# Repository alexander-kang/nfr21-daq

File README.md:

# NFR22's data acquisition system

Repository Contents
-------------------
* **Breakout** - EAGLE design files (.brd, .sch) for the pitot tube breakout board
* **Daughter** - EAGLE design files (.brd, .sch) for the intermediary daughter board
* **Images** - Images for the README's within this repository's subdirectories
* **Main** - EAGLE design files (.brd, .sch) for the main data acquisition board

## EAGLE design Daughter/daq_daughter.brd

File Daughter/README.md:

Board
-----
  
Schematic
---------

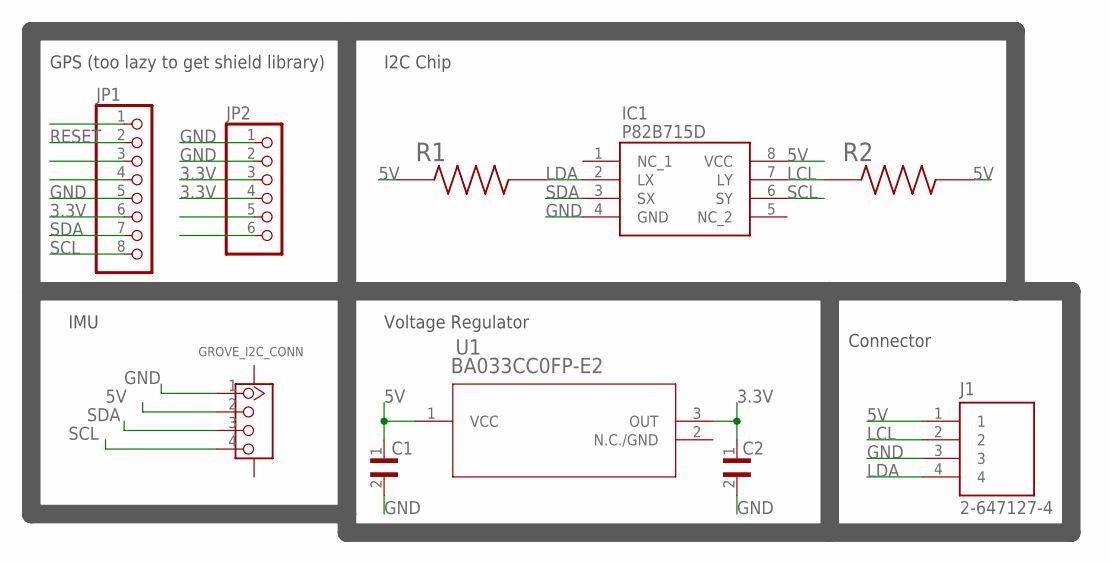
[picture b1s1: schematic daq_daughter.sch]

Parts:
C1, C2: C3216X5R1E106M085AC; CAPC3216X100N
GROVE_I2C_CONN: CONNECTOR-NEW_GROVE-CONNECTOR-SMDDD; CONNECTOR-NEW_HW4-SMD-2.0
IC1: P82B715D; SOIC127P600X175-8N
J1: 2-647127-4; TE_2-647127-4
JP1: PINHD-1X8M; 1X08M
JP2: PINHD-1X6M; 1X06M
R1, R2: RMCF1206JT10K0; RESC3216X70N
U1: BA033CC0FP-E2; TO252-3_ROM

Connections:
3.3V: C2.1, JP1.6, JP2.3, JP2.4, U1.3 (OUT)
5V: C1.1, GROVE_I2C_CONN.2, IC1.8 (VCC), J1.1, R1.1, R2.2, U1.1 (VCC)
GND: C1.2, C2.2, GROVE_I2C_CONN.1, IC1.4 (GND), J1.3, JP1.5, JP2.1, JP2.2
LCL: IC1.7 (LY), J1.2, R2.1
LDA: IC1.2 (LX), J1.4, R1.2
RESET: JP1.2
SCL: GROVE_I2C_CONN.4, IC1.6 (SY), JP1.8
SDA: GROVE_I2C_CONN.3, IC1.3 (SX), JP1.7

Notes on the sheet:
GPS (too lazy to get shield library)
IMU
I2C Chip
Connector
Voltage Regulator

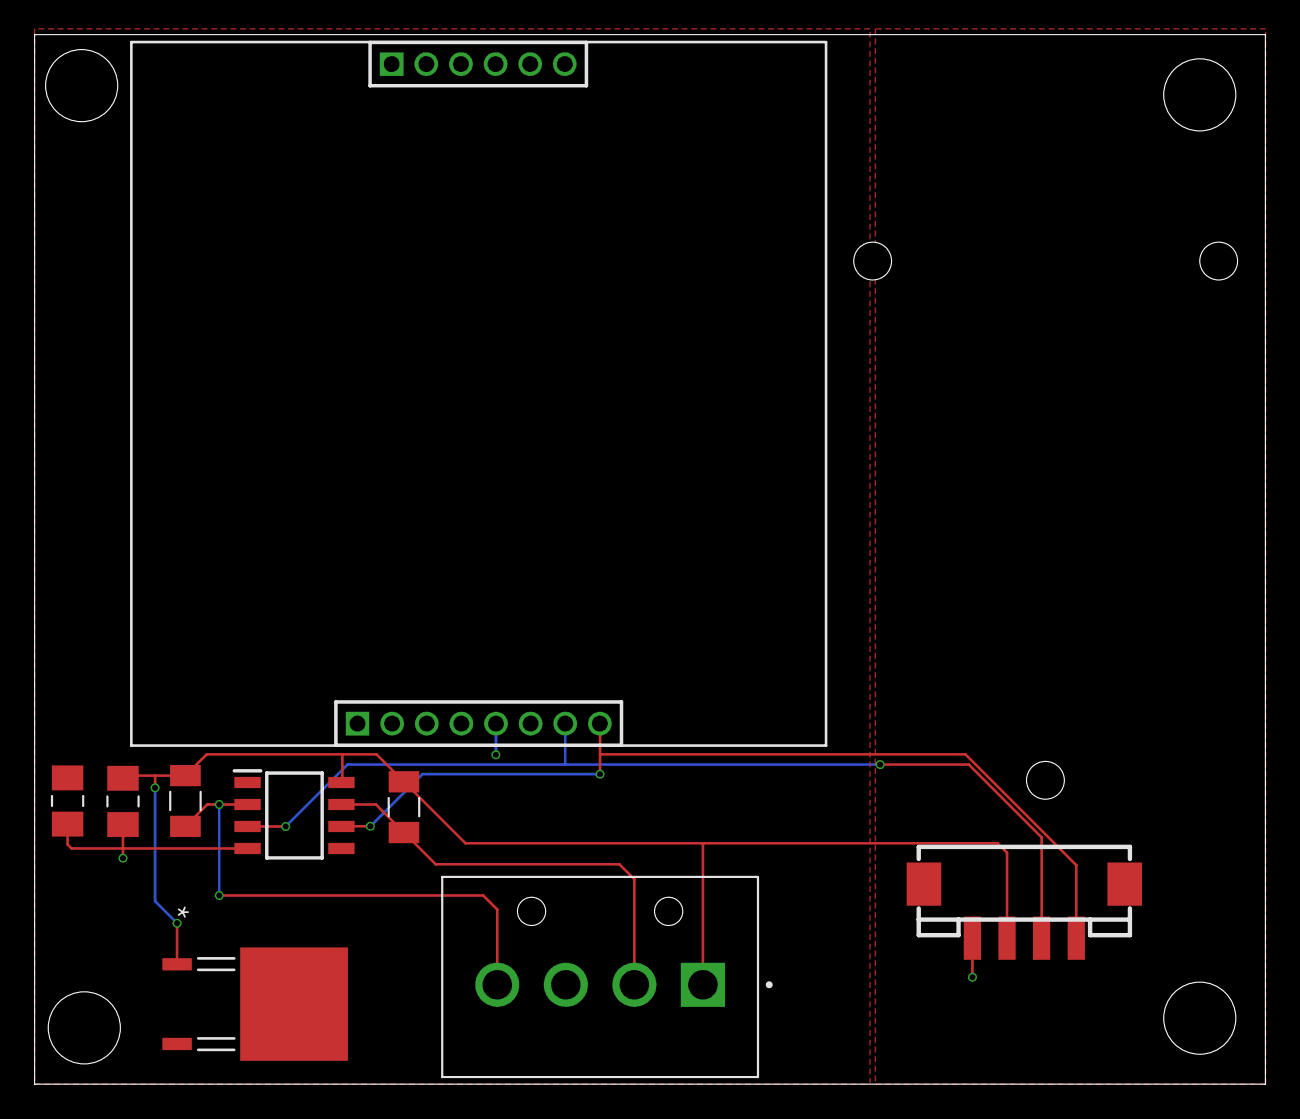
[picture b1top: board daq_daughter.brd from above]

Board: 2 copper layers, 71.1 x 60.6 mm, 10 parts (0 on the bottom side), 7 nets.

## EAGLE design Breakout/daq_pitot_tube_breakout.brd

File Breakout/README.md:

Board
-----
  
Schematic
---------

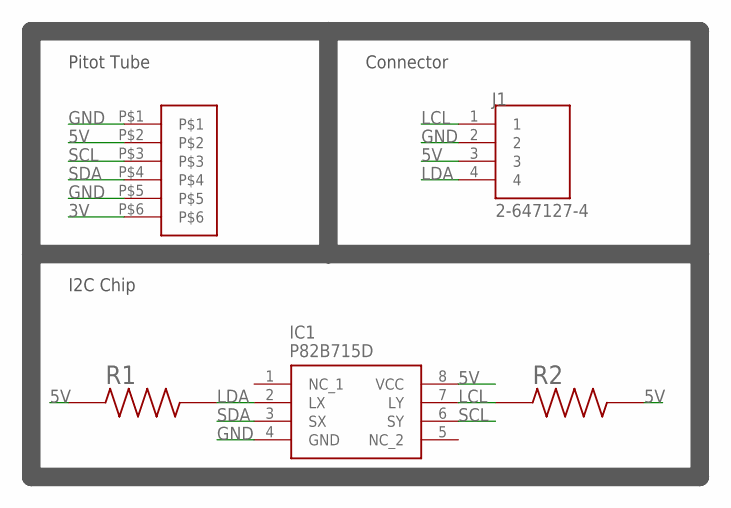
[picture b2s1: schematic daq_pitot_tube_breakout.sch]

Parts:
IC1: P82B715D; SOIC127P600X175-8N
J1: 2-647127-4; TE_2-647127-4
R1, R2: RMCF1206JT10K0; RESC3216X70N
U$1: ASPD-4525

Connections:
3V: U$1.P$6
5V: IC1.8 (VCC), J1.3, R1.1, R2.2, U$1.P$2
GND: IC1.4 (GND), J1.2, U$1.P$1, U$1.P$5
LCL: IC1.7 (LY), J1.1, R2.1
LDA: IC1.2 (LX), J1.4, R1.2
SCL: IC1.6 (SY), U$1.P$3
SDA: IC1.3 (SX), U$1.P$4

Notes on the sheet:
Pitot Tube
I2C Chip
Connector

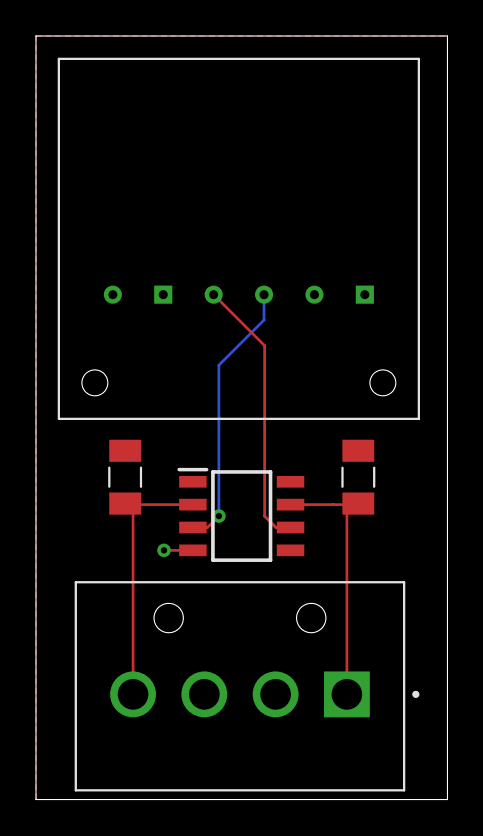
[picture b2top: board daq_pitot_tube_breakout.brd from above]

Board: 2 copper layers, 22.9 x 42.4 mm, 5 parts (0 on the bottom side), 6 nets.

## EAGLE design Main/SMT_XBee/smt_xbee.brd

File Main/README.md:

Directory Contents
------------------
* **SMT_XBee** - EAGLE design files (.brd, .sch) for the main board with a surface-mount XBee (telemetry radio module)
* **Throughhole_XBee** - EAGLE design files (.brd, .sch) for the main board with a through-hole XBee (telemetry radio module)

Board
-----
  
Schematic
---------

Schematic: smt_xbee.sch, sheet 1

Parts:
B1: ARDUINO_MEGA_R3FULL; ARDUINO_MEGA
BRAKEPRES: 156120M173000
BRAKETEMP: 156120M173000
C1, C2, C5, C26: 10μF; C1206
C3, C4: 8.2pF; C1206
C6, C7, C8, C9, C10, C11, C12, C13, C14, C15, C16, C17, C18, C19, C20, C21, C22, C23, C24, C25, C28, C29, C30, C31, C32, C33, C34, C35: 0.1μF; C1206
C27: 22μF; C1206
COOLANTTEMP: 156120M173000
DAQ: 156120M173000
DASH: 156120M173000
E*1: XBEE3PRO_SMT; XBEE3PRO_SMT_FOOTPRINT
IC1: P82B715D; SOIC127P600X175-8N
INTAKEPRES: 156120M173000
INTAKETEMP: 156120M173000
J1: 6473427-1; TE_6473427-1
J2: VR10S05; CONN3_10S05_XPP
JP1: DNP; 1X04
LAMBDAS: 156120M173000
OILPRES: 156120M173000
OILTEMP: 156120M173000
Q1, Q2: MOSFET-NCHANNELSMD; SOT23-3
R1, R2, R3, R4, R11, R12, R13, R14, R15, R16, R17, R18, R19, R20, R21, R22, R23, R24: 1kΩ; R1206
R5, R6, R7, R8, R9, R10, R25, R26, R27, R28, R29, R30, R31, R32, R33, R34, R35, R36, R37, R38, R39, R40, R41, R42, R43, R44, R45, R46, R47, R48, R49, R50, R51, R52, R53, R54, R55, R56, R57, R58, R71: 10kΩ; R1206
R59, R60, R61, R62, R63, R64, R65, R66, R67, R68, R69, R70: 350Ω; R1206
REC: SML-LX1206SIC-TR; LED_SML-LX1206SIC-TR_LUM
SHOCKPOT: 156120M173000
SPARE1, SPARE2: 156120M173000
SW1, SW2: CTS_ELECTROCOMPONENTS_204-211STCTS_ELECTROCOMPONE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; CTS_ELECTROCOMPONENTS_204-211ST_0
U1: XC6220B331MR-G; SOT-25_TOR
U6, U7: ADS1119IPWT; PW0016A_N

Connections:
2AIC0: C28.2, R51.1, U7.11 (AIN0)
2AIC1: C29.2, R52.1, U6.11 (AIN0)
2AIC2: C30.2, R53.1, U7.10 (AIN1)
2AIC3: C31.2, R54.1, U6.10 (AIN1)
3.3V: C2.1, C3.2, C4.2, C5.2, E*1.2, E*1.2-1 (2), R2.2, R4.2, R7.2, R8.1, U1.5 (VOUT)
3AIC0: C32.2, R55.1, U7.7 (AIN2)
3AIC1: C33.2, R56.1, U6.7 (AIN2)
3AIC2: C34.2, R57.1, U7.6 (AIN3)
3AIC3: C35.2, R58.1, U6.6 (AIN3)
4: B1.4, BRAKETEMP.4 (K_GREEN)
5: B1.5, DASH.2 (K_BLUE)
5V: B1.5V@0 (5V), C1.2, C22.2, C23.1, C24.2, C25.1, C27.2, IC1.8 (VCC), J1.12, J1.15, J2.3, JP1.1, Q1.1 (G), Q2.1 (G), R1.2, R3.2, R5.1, R9.1, R10.2, R11.2, R12.2, R13.2, R14.2, R15.2, R16.2, R17.2, R18.2, R19.2, R20.2, R21.2, R22.2, R23.2, R24.1, R41.1, R42.1, R43.2, R44.1, R45.1, R46.2, R47.1, R48.1, R49.1, R50.2, R60.1, R63.1, R66.1, R69.1, SW1.1, SW2.1, U1.1 (VIN), U6.3 (RESET_N), U6.12 (AVDD), U6.13 (DVDD), U7.3 (RESET_N), U7.12 (AVDD), U7.13 (DVDD); also elsewhere on the board
5VOR0V: R61.1, R64.1, R67.1, R70.1, SW1.2
6: B1.6, DASH.3 (K_RED)
7: B1.7, DASH.4 (K_GREEN)
8: B1.8, LAMBDAS.2 (K_BLUE)
9: B1.9, LAMBDAS.3 (K_RED)
10: B1.10, LAMBDAS.4 (K_GREEN)
12V: B1.VIN, C26.2, J1.26, J1.54, J2.1
14: B1.14 (14(TX3)), BRAKETEMP.3 (K_RED)
15: B1.15 (15(RX3)), BRAKETEMP.2 (K_BLUE)
16: B1.16 (16(TX2)), SHOCKPOT.4 (K_GREEN)
17: B1.17 (17(RX2)), SHOCKPOT.3 (K_RED)
18: B1.18 (18(TX1)), SHOCKPOT.2 (K_BLUE)
19: B1.19 (19(RX1)), BRAKEPRES.4 (K_GREEN)
22: B1.22, BRAKEPRES.3 (K_RED)
23: B1.23, BRAKEPRES.2 (K_BLUE)
24: B1.24, INTAKEPRES.4 (K_GREEN)
25: B1.25, INTAKEPRES.3 (K_RED)
26: B1.26, INTAKEPRES.2 (K_BLUE)
27: B1.27, INTAKETEMP.4 (K_GREEN)
28: B1.28, INTAKETEMP.3 (K_RED)
29: B1.29, INTAKETEMP.2 (K_BLUE)
30: B1.30, COOLANTTEMP.4 (K_GREEN)
31: B1.31, COOLANTTEMP.3 (K_RED)
32: B1.32, COOLANTTEMP.2 (K_BLUE)
33: B1.33, OILPRES.4 (K_GREEN)
34: B1.34, OILPRES.3 (K_RED)
35: B1.35, OILPRES.2 (K_BLUE)
36: B1.36, OILTEMP.4 (K_GREEN)
37: B1.37, OILTEMP.3 (K_RED)
38: B1.38, OILTEMP.2 (K_BLUE)
39: B1.39, SPARE1.4 (K_GREEN)
40: B1.40, SPARE1.3 (K_RED)
41: B1.41, SPARE1.2 (K_BLUE)
42: B1.42, SPARE2.4 (K_GREEN)
43: B1.43, SPARE2.3 (K_RED)
44: B1.44, SPARE2.2 (K_BLUE)
45: B1.45, DAQ.4 (K_GREEN)
46: B1.46, DAQ.3 (K_RED)
47: B1.47, DAQ.2 (K_BLUE)
48: B1.48, R71.1, SW2.2
A0: B1.A0 (A0(RX0)), C6.2, R25.2
A0IN: J1.18, R25.1
A1: B1.A1 (A1(TX0)), C7.2, R26.2
A1IN: J1.19, R26.1
A2: B1.A2, C8.2, R27.2
A2IN: J1.20, R27.1
A3: B1.A3, C9.2, R28.2
A3IN: J1.10, R28.1
A4: B1.A4, C10.2, R29.2
A4IN: J1.1, R29.1
A5: B1.A5, C11.2, R30.2
A5IN: J1.11, R30.1
A6: B1.A6, C12.2, R31.2
A6IN: J1.9, R31.1
A7: B1.A7, C13.2, R32.2
A7IN: J1.17, R32.1
A8: B1.A8, C14.2, R33.2
A8IN: J1.8, R33.1
A9: B1.A9, C15.2, R34.2
A9IN: J1.16, R34.1
A10: B1.A10, C16.2, R35.2
A10IN: J1.7, R35.1
A11: B1.A11, C17.2, R36.2
A11IN: J1.6, R36.1
A12: B1.A12, C18.2, R37.2
A12IN: J1.13, R37.1
A13: B1.A13, C19.2, R38.2
A13IN: J1.4, R38.1
A14: B1.A14, C20.2, R39.2
A14IN: J1.5, R39.1
A15: B1.A15, C21.2, R40.2
A15IN: J1.14, R40.1
CALIB: B1.13, J1.31, R50.1
CANHI: J1.60, JP1.3
CANLO: J1.53, JP1.4
CAN_CS: B1.49; also elsewhere on the board
DIN: E*1.4, E*1.4-1 (4), Q1.2 (S), R3.1
DOUT: E*1.3, E*1.3-1 (3), Q2.2 (S), R1.1
FL_WS: B1.2, J1.25, R47.2
FR_WS: B1.3, J1.34, R48.2
GND: B1.GND@0 (GND), C1.1, C2.2, C3.1, C4.1, C5.1, C6.1, C7.1, C8.1, C9.1, C10.1, C11.1, C12.1, C13.1, C14.1, C15.1, C16.1, C17.1, C18.1, C19.1, C20.1, C21.1, C22.1, C23.2, C24.1, C25.2, C26.1, C27.1, C28.1, C29.1, C30.1, C31.1, C32.1, C33.1, C34.1, C35.1, E*1.1, E*1.1-1 (1), E*1.11, E*1.11-1 (11), E*1.13, E*1.13-1 (13), E*1.22, E*1.22-1 (22), E*1.35, E*1.35-1 (35), E*1.38 (0), E*1.38-1 (0), E*1.38-2 (0), E*1.38-3 (0), E*1.38-4 (0), E*1.38-5 (0), E*1.38-6 (0), E*1.38-7 (0), E*1.38-8 (0), E*1.38-9 (0), IC1.4 (GND), J1.21, J1.22, J1.23, J1.24, J1.50, J1.51, J1.52, J2.2, JP1.2, R6.1, R59.2, R62.2, R65.2, R68.2, R71.2, U1.2 (VSS), U6.4 (DGND), U6.5 (AGND), U7.4 (DGND), U7.5 (AGND); also elsewhere on the board
LCL: IC1.7 (LY), J1.35, J1.36, J1.37, J1.38, J1.39, J1.40, J1.41, J1.42, J1.43, J1.44, J1.45, J1.46, J1.47, J1.48, J1.49, J1.57, R10.1
LDA: IC1.2 (LX), J1.32, R9.2
MISO: B1.50; also elsewhere on the board
MOSI: B1.51; also elsewhere on the board
unnamed: INTAKEPRES.1 (COMMON_ANODE), R16.1
unnamed: R5.2, R6.2, U1.3 (CE)
unnamed: DASH.1 (COMMON_ANODE), R11.1
unnamed: INTAKETEMP.1 (COMMON_ANODE), R17.1
unnamed: COOLANTTEMP.1 (COMMON_ANODE), R18.1
unnamed: OILPRES.1 (COMMON_ANODE), R19.1
unnamed: OILTEMP.1 (COMMON_ANODE), R20.1
unnamed: R21.1, SPARE1.1 (COMMON_ANODE)
unnamed: R22.1, SPARE2.1 (COMMON_ANODE)
unnamed: DAQ.1 (COMMON_ANODE), R23.1
unnamed: R24.2, REC.2
unnamed: E*1.10, E*1.10-1 (10), R8.2
unnamed: R43.1, U6.14 (DRDY_N)
unnamed: LAMBDAS.1 (COMMON_ANODE), R12.1
unnamed: BRAKETEMP.1 (COMMON_ANODE), R13.1
unnamed: R14.1, SHOCKPOT.1 (COMMON_ANODE)
unnamed: BRAKEPRES.1 (COMMON_ANODE), R15.1
unnamed: E*1.29, E*1.29-1 (29), R7.1
unnamed: R51.2, R59.1, R60.2
unnamed: R53.2, R62.1, R63.2
unnamed: R46.1, U7.14 (DRDY_N)
unnamed: R55.2, R65.1, R66.2
unnamed: R41.2, U6.9 (REFP)
unnamed: R42.2, U6.8 (REFN)
unnamed: R44.2, U7.9 (REFP)
unnamed: R45.2, U7.8 (REFN)
unnamed: R57.2, R68.1, R69.2
REC: B1.11, J1.33, R49.2, REC.1
RX0: B1.0 (0(RX0)), Q2.3 (D), R2.1
SCK: B1.52; also elsewhere on the board
SCL: B1.21 (21(SCL)), IC1.6 (SY), U6.2 (A1), U6.16 (SCL), U7.1 (A0), U7.16 (SCL)
SDA: B1.20 (20(SDA)), IC1.3 (SX), U6.1 (A0), U6.15 (SDA), U7.2 (A1), U7.15 (SDA)
SD_CS: B1.53; also elsewhere on the board
SG_11: J1.30, R58.2, R70.2
SG_21: J1.29, R56.2, R67.2
SG_31: J1.28, R54.2, R64.2
SG_41: J1.27, R52.2, R61.2
TX0: B1.1 (1(TX0)), Q1.3 (D), R4.1

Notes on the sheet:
Analog inputs
Indicator LEDs
ADCs
Arduino Mega
Wheatstone bridges
Connectors
Peripherals
CAN/SD shield
XBee
I2C Buffer
Buck converter

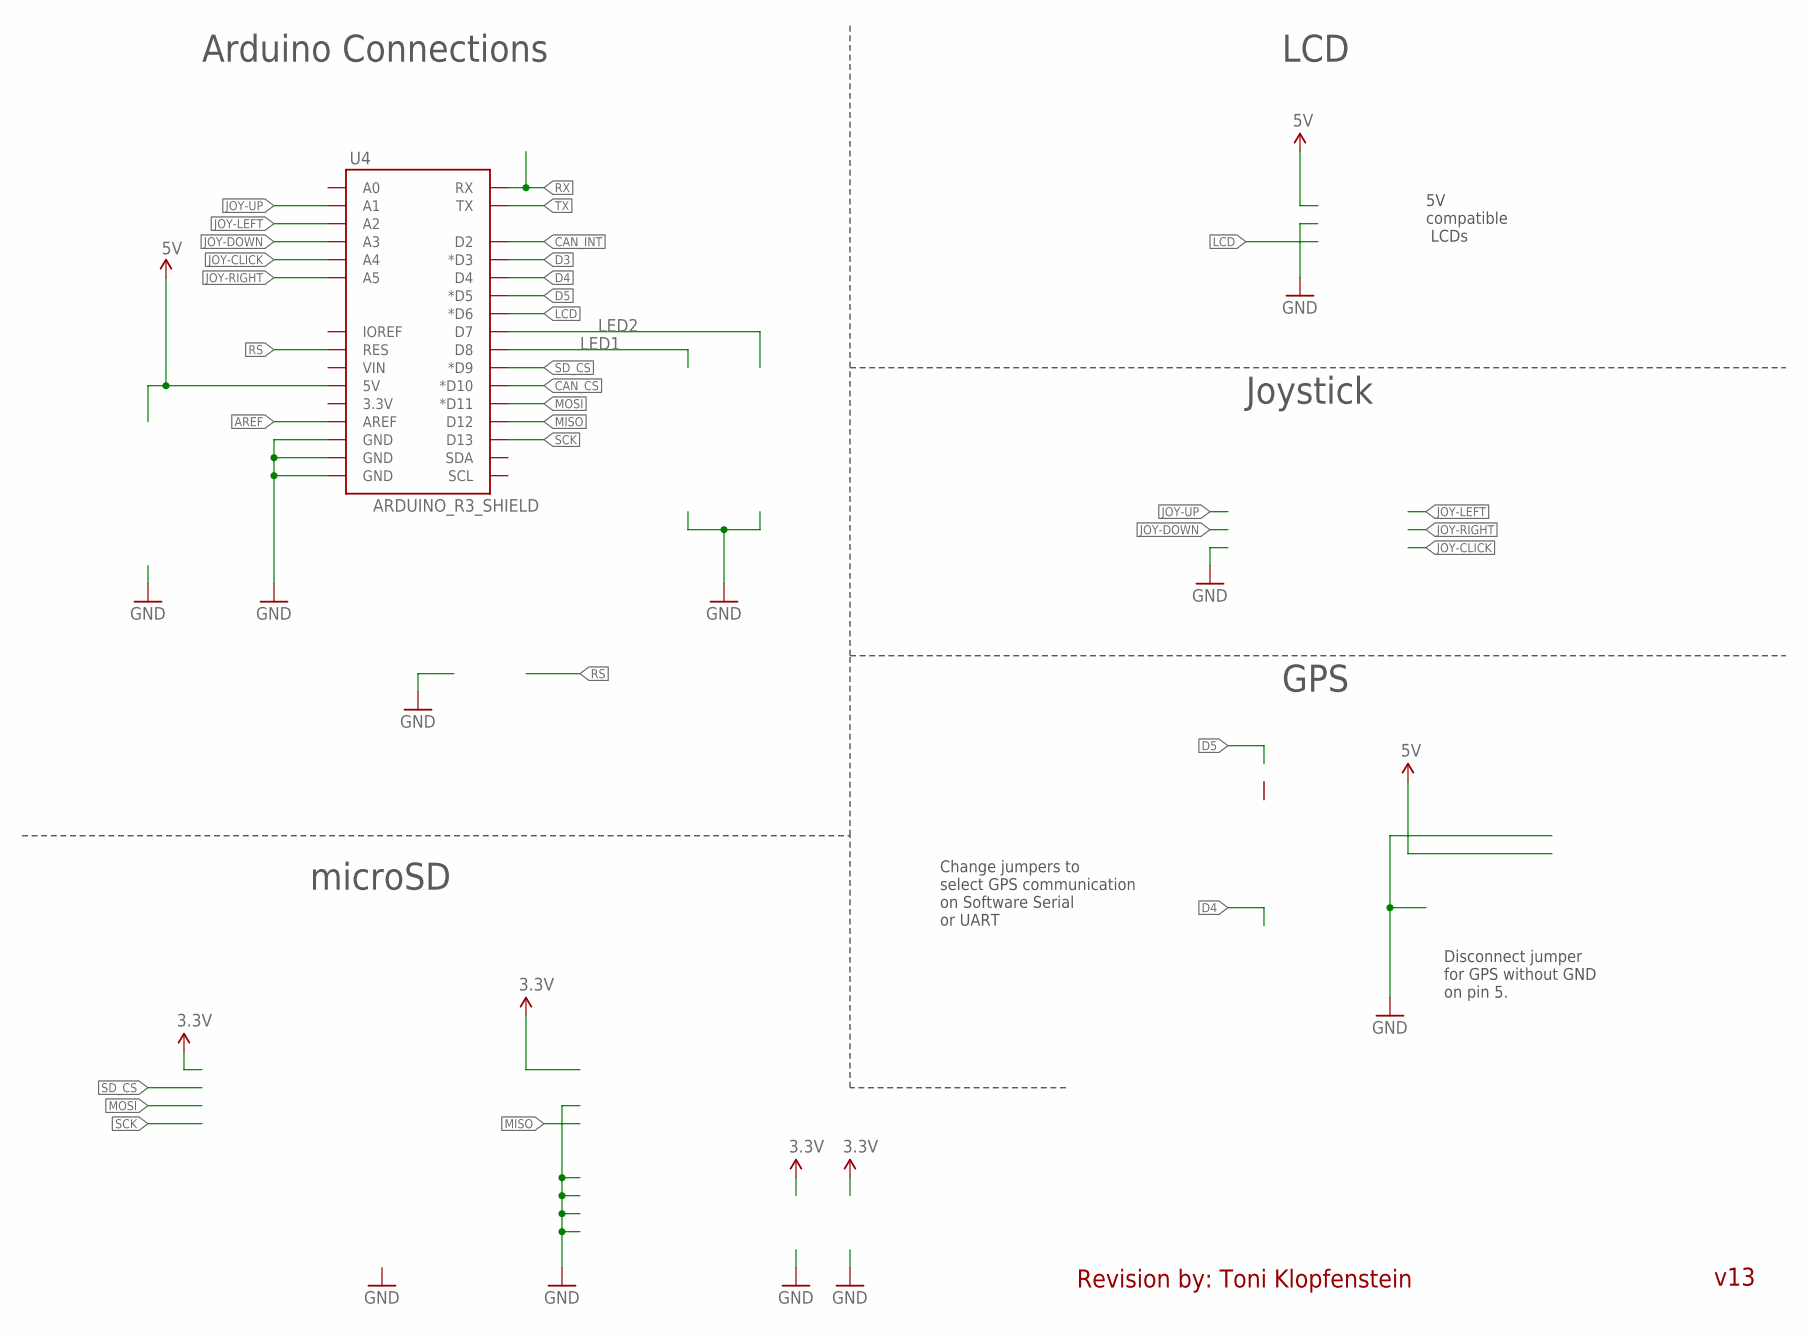
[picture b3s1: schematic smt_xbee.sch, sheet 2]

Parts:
U4: ARDUINO_R3_SHIELD; UNO_R3_SHIELD

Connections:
5V: U4.5V; also elsewhere on the board
AREF: U4.AREF
CAN_CS: U4.D10 (*D10); also elsewhere on the board
CAN_INT: U4.D2
D3: U4.D3 (*D3)
D4: U4.D4
D5: U4.D5 (*D5)
GND: U4.GND@0 (GND), U4.GND@1 (GND), U4.GND@2 (GND); also elsewhere on the board
JOY-CLICK: U4.A4
JOY-DOWN: U4.A3
JOY-LEFT: U4.A2
JOY-RIGHT: U4.A5
JOY-UP: U4.A1
LCD: U4.D6 (*D6)
LED1: U4.D8
LED2: U4.D7
MISO: U4.D12; also elsewhere on the board
MOSI: U4.D11 (*D11); also elsewhere on the board
RS: U4.RES
RX: U4.RX
SCK: U4.D13; also elsewhere on the board
SD_CS: U4.D9 (*D9); also elsewhere on the board
TX: U4.TX

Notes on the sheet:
Arduino Connections
LCD
Joystick
5V compatible LCDs
GPS
Change jumpers to select GPS communication on Software Serial or UART
Disconnect jumper for GPS without GND on pin 5.
microSD
Revision by: Toni Klopfenstein
v13

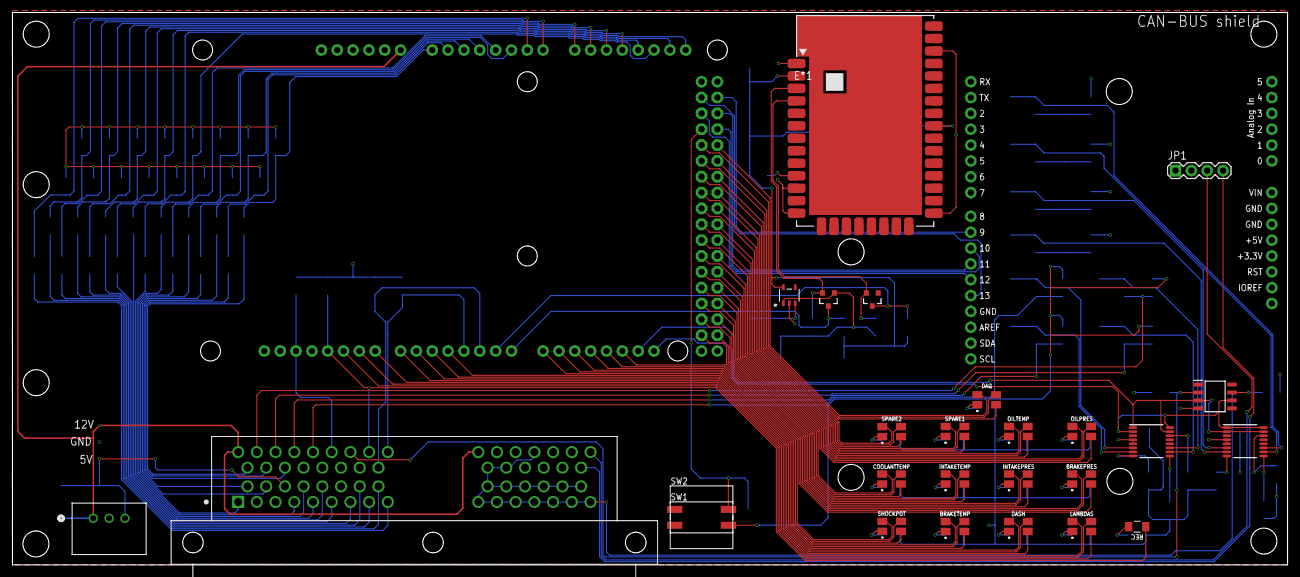
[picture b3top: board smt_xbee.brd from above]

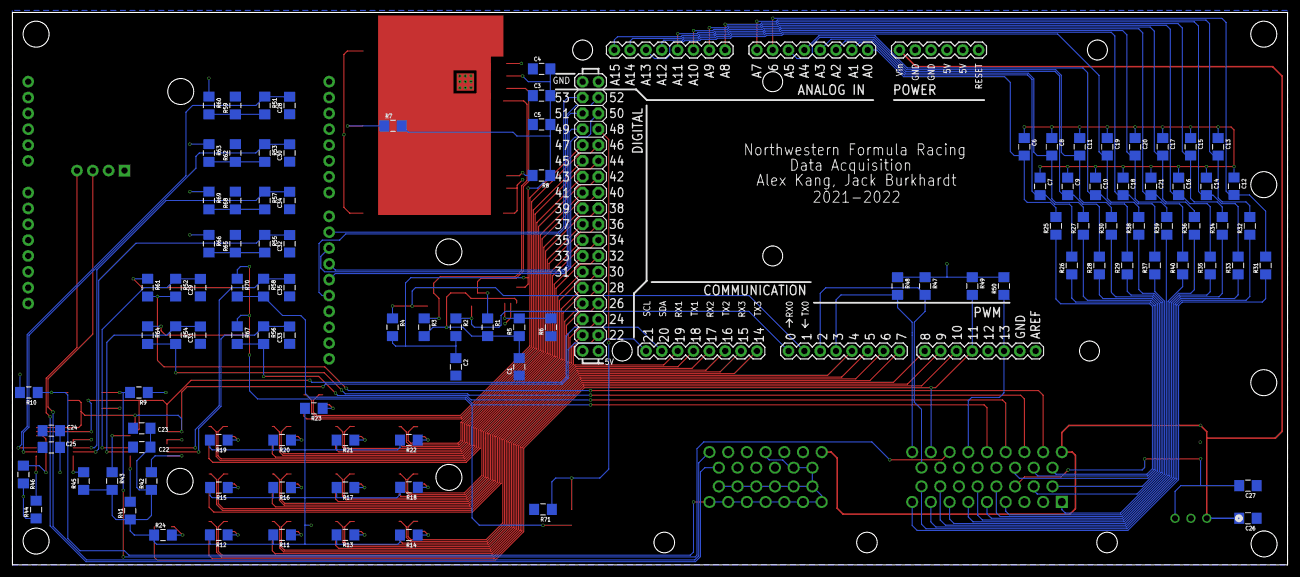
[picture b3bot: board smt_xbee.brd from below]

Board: 2 copper layers, 204.4 x 88.6 mm, 134 parts (107 on the bottom side), 135 nets.

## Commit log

2022-12-09 added HW files
2022-12-09 added/edited README's
2022-12-09 fixing README's
2022-12-09 another fix to README's
2022-12-09 added content to Main/README.md

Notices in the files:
parts and their libraries:
COPYRIGHT: Copyright (C) 2022 Ultra Librarian. All rights reserved.
SparkFun-Boards: Licensing: Creative Commons ShareAlike 4.0 International - https://creativecommons.org/licenses/by-sa/4.0
COPYRIGHT: Copyright (C) 2021 Ultra Librarian. All rights reserved.
